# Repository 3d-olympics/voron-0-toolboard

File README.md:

# USB toolhead board for Voron 0.2

This board replaces the strain relief part at the back of the Voron 0.2's toolhead. It receives 24V through the a USB-C cable - a companion board/connector allows this power voltage to be injected between your RPi and the USB-C cable to this toolboard.
This is non-standard and not really advisable, so proceed at your own risk!

https://youtu.be/3sF8bKx-5_M

## Features
* ADXL345 accelerometer, with interrupt pin connected for use as a "probe"
* TMC2209 driver for extruder motor
* STM32F042G6U6TR, 28-pin microcontroller for running Klipper
* USB-C connector with strain relief
* Connectors for heater and two thermistors
* Connector for a probe or other device e.g. LEDs
* Connectors for hotend fan and two cooling fans
* 5V buck regulator - hotend and cooling fans can separately be supplied with 5 or 24V

The project is developed in KiCad, and that's what the project files are for.

If there's any interest I'll provide some more material like gerber and BOM files.

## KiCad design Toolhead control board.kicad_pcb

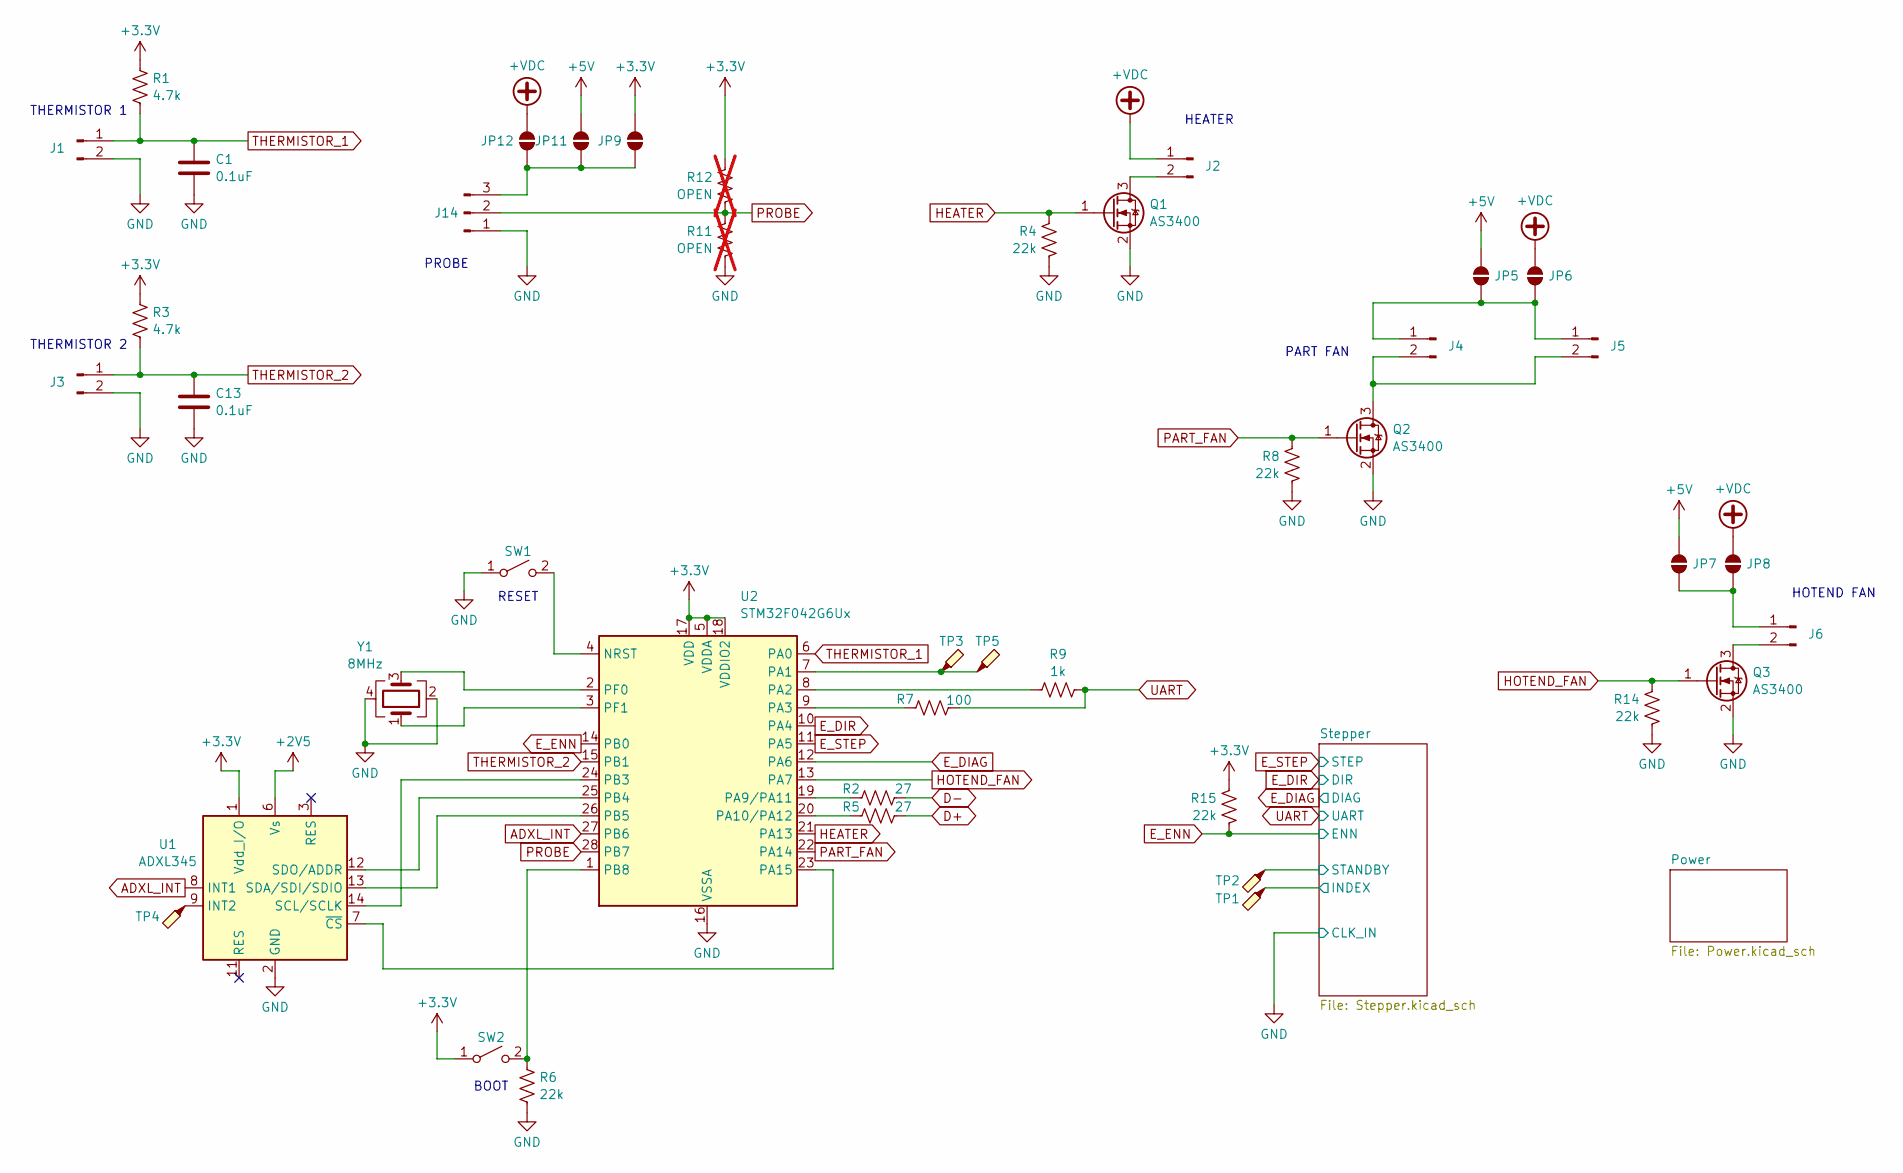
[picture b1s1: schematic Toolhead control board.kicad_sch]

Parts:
C1, C13: 0.1uF; C_0603_1608Metric
J1, J3, J4, J5, J6: Conn_01x02_Pin; JST_XH_B2B-XH-A_1x02_P2.50mm_Vertical
J2: Conn_01x02_Pin; TerminalBlock_Phoenix_PT-1,5-2-3.5-H_1x02_P3.50mm_Horizontal
J14: Conn_01x04_Male; JST_XH_S3B-XH-A-1_1x03_P2.50mm_Horizontal
JP5, JP6, JP7, JP8, JP9, JP11, JP12: SolderJumper_2_Open; SolderJumper-2_P1.3mm_Open_TrianglePad1.0x1.5mm
Q1, Q2, Q3: AS3400; SOT-23
R1, R3: 4.7k; R_0603_1608Metric
R2, R5: 27; R_0603_1608Metric
R4, R6, R8, R14, R15: 22k; R_0603_1608Metric
R7: 100; R_0603_1608Metric
R9: 1k; R_0603_1608Metric
R11, R12: OPEN; R_0603_1608Metric; not fitted
SW1, SW2: SW_SPST; SW_SPST_B3U-1000P
TP1, TP2, TP3, TP4, TP5: TestPoint_Probe; TestPoint_Pad_D1.0mm
U1: ADXL345; LGA-14_3x5mm_P0.8mm_LayoutBorder1x6y
U2: STM32F042G6Ux; QFN-28_4x4mm_P0.5mm
Y1: 8MHz; Crystal_SMD_3225-4Pin_3.2x2.5mm

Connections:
+2V5: U1.6 (Vs); also elsewhere on the board
+3.3V: JP9.2 (B), R1.1, R3.1, R12.1, R15.1, SW2.1 (A), U1.1 (Vdd_I/O), U2.5 (VDDA), U2.17 (VDD), U2.18 (VDDIO2); also elsewhere on the board
+5V: JP5.2 (B), JP7.2 (B), JP11.2 (B); also elsewhere on the board
+VDC: J2.1, JP6.2 (B), JP8.2 (B), JP12.2 (B); also elsewhere on the board
/Stepper/INDEX: TP1.1; also elsewhere on the board
/Stepper/STANDBY: TP2.1; also elsewhere on the board
ADXL_INT: U1.8 (INT1), U2.27 (PB6)
D+: R5.2; also elsewhere on the board
D-: R2.2; also elsewhere on the board
E_DIAG: U2.12 (PA6); also elsewhere on the board
E_DIR: U2.10 (PA4); also elsewhere on the board
E_ENN: R15.2, U2.14 (PB0); also elsewhere on the board
E_STEP: U2.11 (PA5); also elsewhere on the board
GND: C1.2, C13.2, J1.2, J3.2, J14.1, Q1.2 (S), Q2.2 (S), Q3.2 (S), R4.2, R6.2, R8.2, R11.2, R14.2, SW1.1 (A), U1.2 (GND), U1.4 (GND), U1.5 (GND), U2.16 (VSSA), Y1.2, Y1.4; also elsewhere on the board
HEATER: Q1.1 (G), R4.1, U2.21 (PA13)
HOTEND_FAN: Q3.1 (G), R14.1, U2.13 (PA7)
unnamed 18: J2.2, Q1.3 (D); also elsewhere on the board
unnamed: J4.1, J5.1, JP5.1 (A), JP6.1 (A)
unnamed: J4.2, J5.2, Q2.3 (D)
unnamed: J6.1, JP7.1 (A), JP8.1 (A)
unnamed: J6.2, Q3.3 (D)
unnamed: J14.3, JP9.1 (A), JP11.1 (A), JP12.1 (A)
unnamed: SW1.2 (B), U2.4 (NRST)
unnamed: R6.1, SW2.2 (B), U2.1 (PB8)
unnamed: TP4.1, U1.9 (INT2)
unnamed: U1.14 (SCL/SCLK), U2.24 (PB3)
unnamed: U1.13 (SDA/SDI/SDIO), U2.26 (PB5)
unnamed: U1.12 (SDO/ADDR), U2.25 (PB4)
unnamed: U1.7 (~CS), U2.23 (PA15)
unnamed: TP3.1, TP5.1, U2.7 (PA1)
unnamed: R9.1, U2.8 (PA2)
unnamed: R7.1, U2.9 (PA3)
unnamed: R2.1, U2.19 (PA9/PA11)
unnamed: R5.1, U2.20 (PA10/PA12)
unnamed: U2.2 (PF0), Y1.3
unnamed: U2.3 (PF1), Y1.1
PART_FAN: Q2.1 (G), R8.1, U2.22 (PA14)
PROBE: J14.2, R11.1, R12.2, U2.28 (PB7)
THERMISTOR_1: C1.1, J1.1, R1.2, U2.6 (PA0)
THERMISTOR_2: C13.1, J3.1, R3.2, U2.15 (PB1)
UART: R7.2, R9.2; also elsewhere on the board

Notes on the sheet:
PROBE
HOTEND FAN
PART FAN
THERMISTOR 1
THERMISTOR 2
BOOT
HEATER
RESET

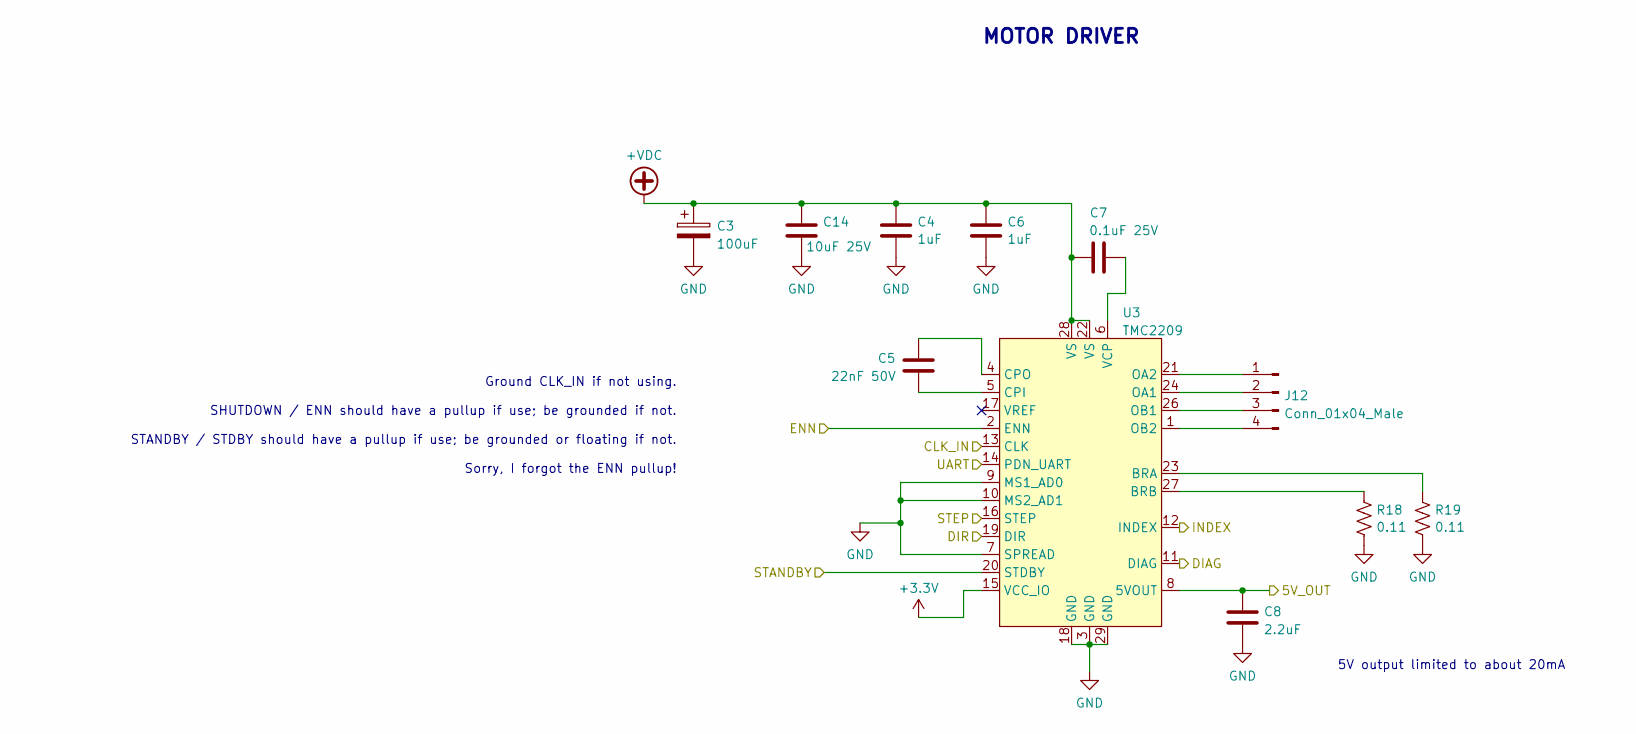
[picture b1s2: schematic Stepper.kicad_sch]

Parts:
C3: 100uF; CP_Radial_D6.3mm_P2.50mm
C4, C6: 1uF; C_0603_1608Metric
C5: 22nF 50V; C_0603_1608Metric
C7: 0.1uF 25V; C_0603_1608Metric
C8: 2.2uF; C_0603_1608Metric
C14: 10uF 25V; C_0805_2012Metric
J12: Conn_01x04_Male; JST_XH_S4B-XH-A-1_1x04_P2.50mm_Horizontal
R18, R19: 0.11; R_1206_3216Metric
U3: TMC2209; QFN-28-1EP_5x5mm_P0.5mm_EP3.35x3.35mm

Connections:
+3.3V: U3.15 (VCC_IO); also elsewhere on the board
+VDC: C3.1, C4.1, C6.1, C7.1, C14.1, U3.22 (VS), U3.28 (VS); also elsewhere on the board
/Stepper/5V_OUT: C8.1, U3.8 (5VOUT)
/Stepper/INDEX: U3.12 (INDEX); also elsewhere on the board
/Stepper/STANDBY: U3.20 (STDBY); also elsewhere on the board
E_DIAG: U3.11 (DIAG); also elsewhere on the board
E_DIR: U3.19 (DIR); also elsewhere on the board
E_ENN: U3.2 (ENN); also elsewhere on the board
E_STEP: U3.16 (STEP); also elsewhere on the board
GND: C3.2, C4.2, C6.2, C8.2, C14.2, R18.2, R19.2, U3.3 (GND), U3.7 (SPREAD), U3.9 (MS1_AD0), U3.10 (MS2_AD1), U3.13 (CLK), U3.18 (GND), U3.29 (GND); also elsewhere on the board
unnamed: J12.1, U3.21 (OA2)
unnamed: J12.2, U3.24 (OA1)
unnamed: J12.3, U3.26 (OB1)
unnamed: J12.4, U3.1 (OB2)
unnamed: R19.1, U3.23 (BRA)
unnamed: R18.1, U3.27 (BRB)
unnamed: C5.2, U3.5 (CPI)
unnamed: C5.1, U3.4 (CPO)
unnamed: C7.2, U3.6 (VCP)
UART: U3.14 (PDN_UART); also elsewhere on the board

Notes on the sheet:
5V output limited to about 20mA
MOTOR DRIVER
Ground CLK_IN if not using. SHUTDOWN / ENN should have a pullup if use; be grounded if not. STANDBY / STDBY should have a pullup if use; be grounded or floating if not. Sorry, I forgot the ENN pullup!

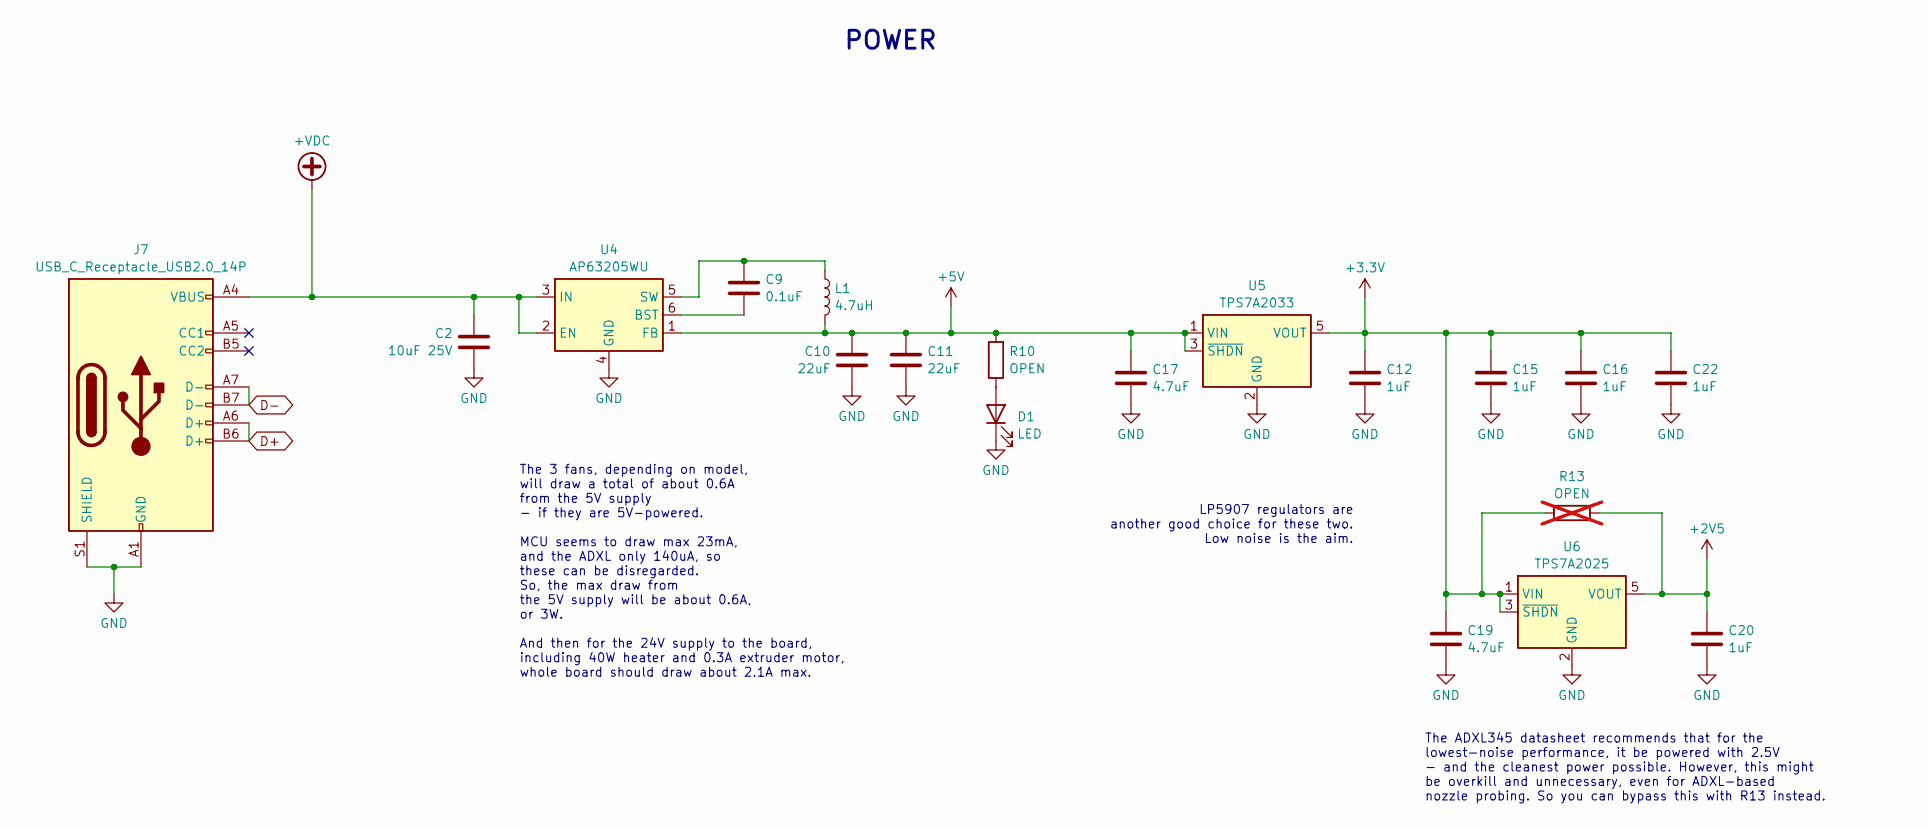
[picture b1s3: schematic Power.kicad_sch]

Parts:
C2: 10uF 25V; C_0805_2012Metric
C9: 0.1uF; C_0603_1608Metric
C10, C11: 22uF; C_0805_2012Metric
C12, C15, C16, C20, C22: 1uF; C_0603_1608Metric
C17, C19: 4.7uF; C_0805_2012Metric
D1: LED; LED_0603_1608Metric
J7: USB_C_Receptacle_USB2.0_14P; USB_C_Receptacle_GCT_USB4085
L1: 4.7uH; L_Taiyo-Yuden_MD-3030
R10: OPEN; R_0603_1608Metric
R13: OPEN; R_0603_1608Metric; not fitted
U4: AP63205WU; TSOT-23-6
U5: TPS7A2033; SOT-23-5
U6: TPS7A2025; SOT-23-5

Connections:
+2V5: C20.1, R13.2, U6.5 (VOUT); also elsewhere on the board
+3.3V: C12.1, C15.1, C16.1, C19.1, C22.1, R13.1, U5.5 (VOUT), U6.1 (VIN), U6.3 (~SHDN); also elsewhere on the board
+5V: C10.1, C11.1, C17.1, L1.2, R10.2, U4.1 (FB), U5.1 (VIN), U5.3 (~SHDN); also elsewhere on the board
+VDC: C2.1, J7.A4 (VBUS), J7.A9 (VBUS), J7.B4 (VBUS), J7.B9 (VBUS), U4.2 (EN), U4.3 (IN); also elsewhere on the board
D+: J7.A6 (D+), J7.B6 (D+); also elsewhere on the board
D-: J7.A7 (D-), J7.B7 (D-); also elsewhere on the board
GND: C2.2, C10.2, C11.2, C12.2, C15.2, C16.2, C17.2, C19.2, C20.2, C22.2, D1.1 (K), J7.A1 (GND), J7.A12 (GND), J7.B1 (GND), J7.B12 (GND), J7.S1 (SHIELD), U4.4 (GND), U5.2 (GND), U6.2 (GND); also elsewhere on the board
unnamed: D1.2 (A), R10.1
unnamed: C9.2, U4.6 (BST)
unnamed: C9.1, L1.1, U4.5 (SW)

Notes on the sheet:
The ADXL345 datasheet recommends that for the lowest-noise performance, it be powered with 2.5V - and the cleanest power possible. However, this might be overkill and unnecessary, even for ADXL-based nozzle probing. So you can bypass this with R13 instead.
POWER
LP5907 regulators are another good choice for these two. Low noise is the aim.
The 3 fans, depending on model, will draw a total of about 0.6A from the 5V supply - if they are 5V-powered. MCU seems to draw max 23mA, and the ADXL only 140uA, so these can be disregarded. So, the max draw from the 5V supply will be about 0.6A, or 3W. And then for the 24V supply to the board, inc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

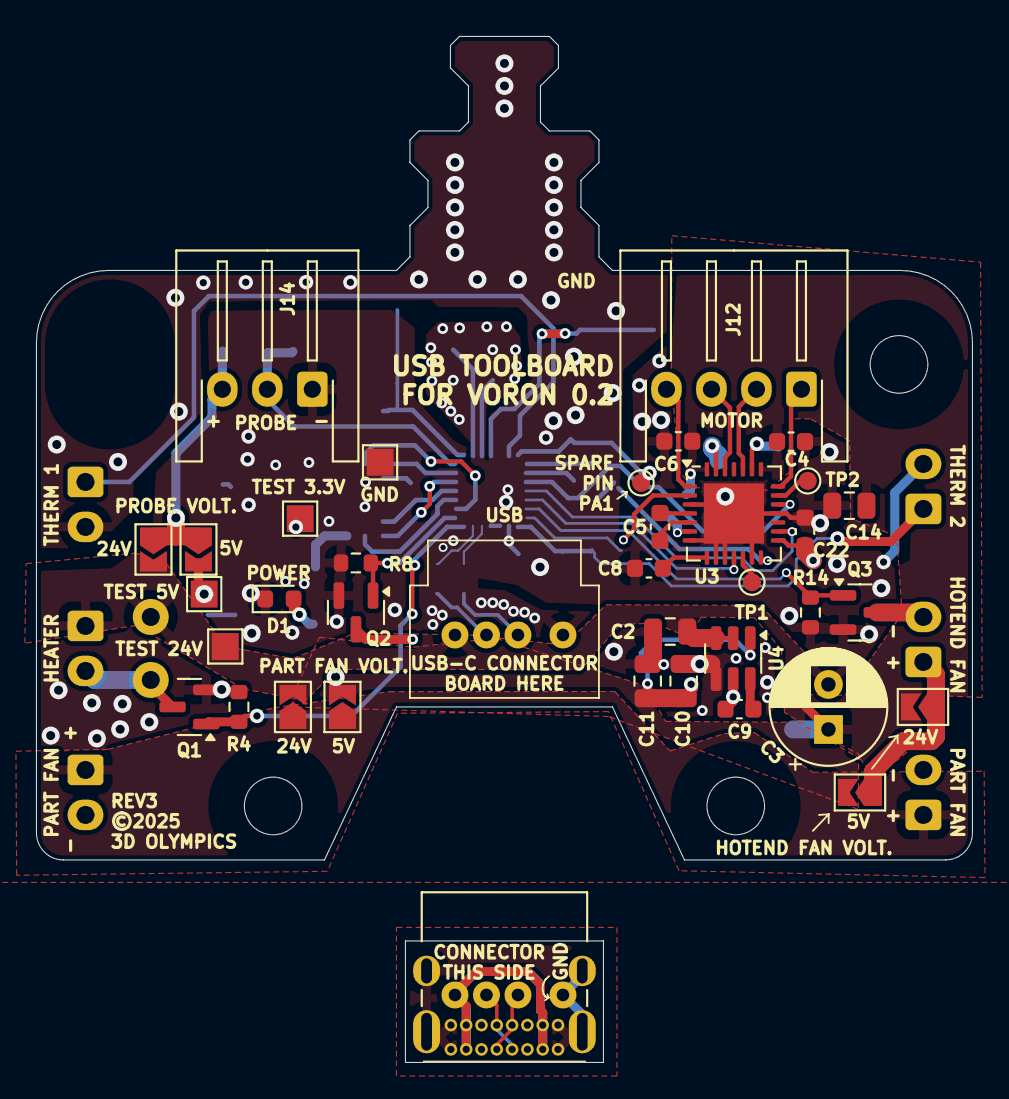
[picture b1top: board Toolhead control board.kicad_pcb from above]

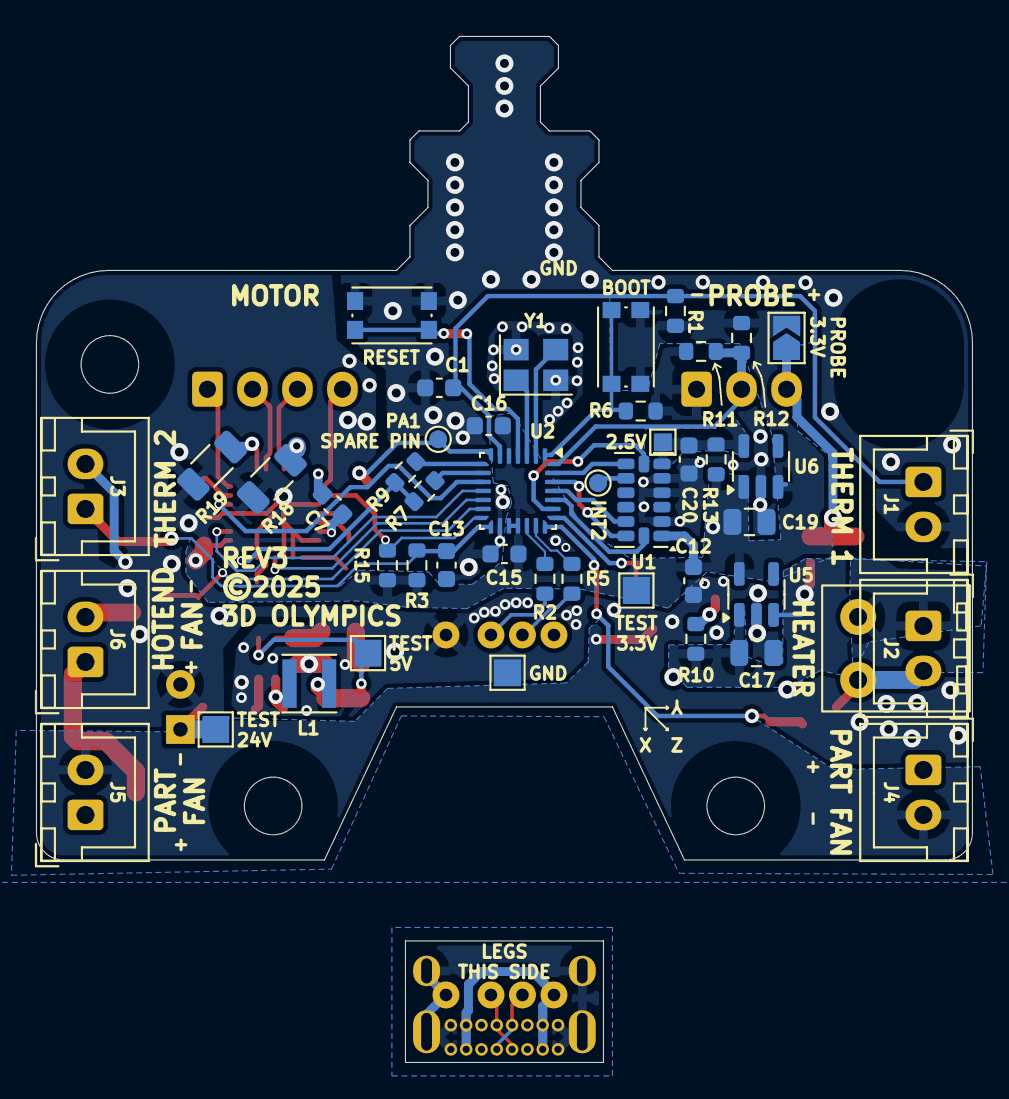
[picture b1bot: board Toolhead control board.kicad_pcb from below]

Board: 2 copper layers, 52.0 x 57.0 mm, 73 parts (41 on the bottom side), 54 nets.

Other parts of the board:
J2#2: Conn_01x02_Pin; JST_XH_B2B-XH-A_1x02_P2.50mm_Vertical

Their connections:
+VDC: J2#2.1; also elsewhere on the board
unnamed 18: J2#2.2; also elsewhere on the board

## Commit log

2025-09-25 Initial commit. Old version with programmer interface, no probe, etc
2025-09-30 Rev1. Uart interface
2025-10-02 Rev2 (USB) largely done
2025-10-22 Rev2, as ordered
2025-10-26 Rev3 (connectors on back, and with USB daughter board) - probably done
2025-10-27 Rev3 as ordered
2025-10-27 Create LICENSE
2026-01-06 Little changes while populating
2026-01-06 Oops I'd saved a test thing accidentally

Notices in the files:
Toolhead control board.kicad_pcb:
©2025
